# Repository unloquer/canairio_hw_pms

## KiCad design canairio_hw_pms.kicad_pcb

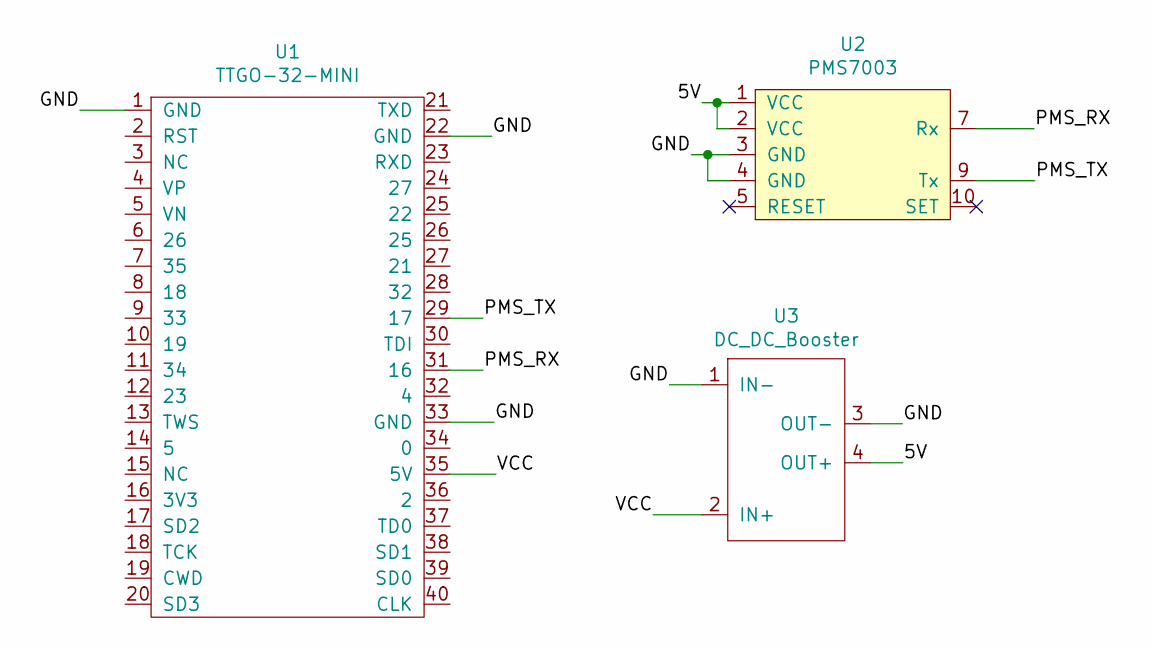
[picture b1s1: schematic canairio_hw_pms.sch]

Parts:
U1: TTGO-32-MINI
U2: PMS7003
U3: DC_DC_Booster

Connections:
/5V: U2.1 (VCC), U2.2 (VCC), U3.4 (OUT+)
/GND: U1.1 (GND), U1.22 (GND), U1.33 (GND), U2.3 (GND), U2.4 (GND), U3.1 (IN-), U3.3 (OUT-)
/PMS_RX: U1.31 (16), U2.7 (Rx)
/PMS_TX: U1.29 (17), U2.9 (Tx)
/VCC: U1.35 (5V), U3.2 (IN+)

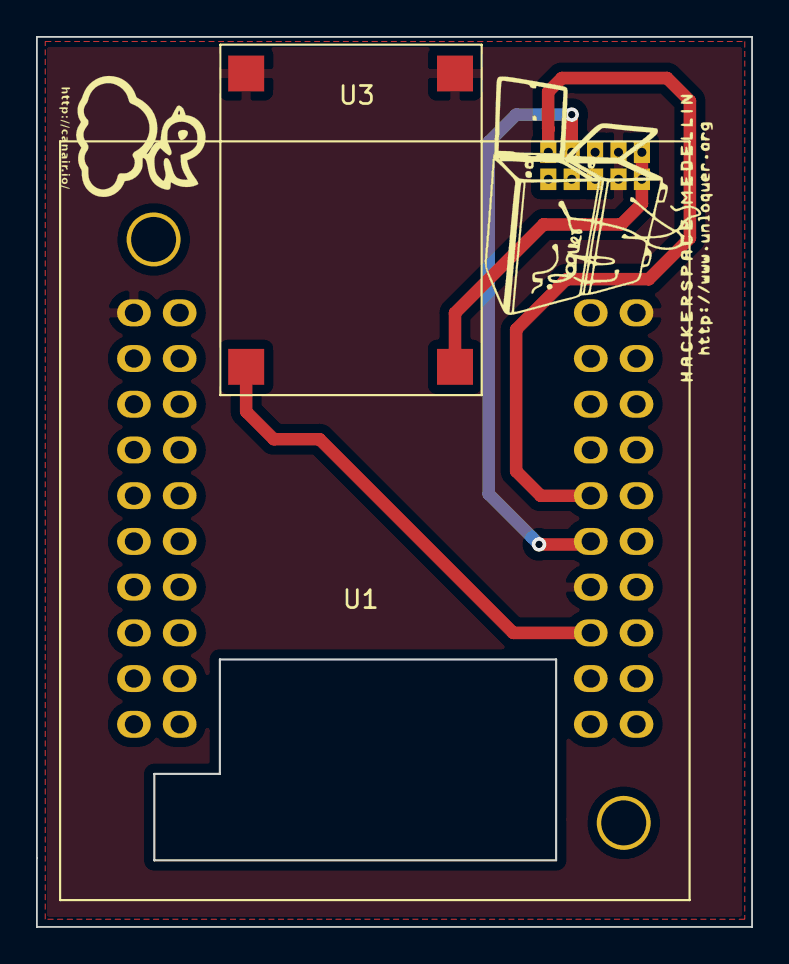
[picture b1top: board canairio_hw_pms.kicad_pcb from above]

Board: 2 copper layers, 39.7 x 49.4 mm, 3 parts (1 on the bottom side), 5 nets.

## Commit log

2020-01-18 Integra hardware de canair.io con sensor Plantower PMS7003
